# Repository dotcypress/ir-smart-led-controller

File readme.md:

# lantern-controller

IR Remote Controller for my lantern.

## Resources

- [Schematics](pcb/ir-smart-led-controller.pdf)
- [Gerber files](pcb/ir-smart-led-controller.zip)
- [BOM](pcb/ir-smart-led-controller.csv)

## License

Licensed under either of

- Apache License, Version 2.0 ([LICENSE-APACHE](LICENSE-APACHE) or
  http://www.apache.org/licenses/LICENSE-2.0)
- MIT license ([LICENSE-MIT](LICENSE-MIT) or http://opensource.org/licenses/MIT)

at your option.

### Contribution

Unless you explicitly state otherwise, any contribution intentionally submitted
for inclusion in the work by you, as defined in the Apache-2.0 license, shall be
dual licensed as above, without any additional terms or conditions.

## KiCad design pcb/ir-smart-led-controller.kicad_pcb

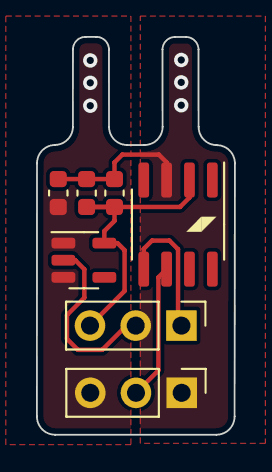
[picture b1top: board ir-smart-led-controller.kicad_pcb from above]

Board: 2 copper layers, 11.0 x 22.1 mm, 7 parts (0 on the bottom side), 5 nets.

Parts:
C1, C2, C3: C; C_0603_1608Metric
J1: Conn_01x03; PinHeader_1x03_P2.54mm_Vertical
U1: STM32G030J6Mx; SOIC-8_3.9x4.9mm_P1.27mm
U2: TSSP58038; PinHeader_1x03_P2.54mm_Vertical
U3: LDK220; SOT-23-5

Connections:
+5V: C1.1, J1.3, U3.1 (IN), U3.3 (EN)
GND: C1.2, C2.2, C3.2, J1.1, U1.3 (GND), U2.2 (GND), U3.2 (GND)
unnamed: J1.2, U1.6 (PA12)
unnamed: U1.5 (PA11), U2.1 (OUT)
VDD: C2.1, C3.1, U1.2 (VDD), U2.3 (Vs), U3.5 (OUT)

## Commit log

2021-05-19 0.0.1
2021-05-22 safety added
2021-05-22 cleanup
2021-06-13 Add rust-toolchain config
2021-07-25 overheat protection
2021-12-26 update deps
2022-11-06 update hal
2022-11-28 lantern fire animation
